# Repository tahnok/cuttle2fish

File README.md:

# Cuttle2Fish

Something you know (password) and something you have (cuttlefish shaped U2F token)

Based on the STM32F103

## Software

Intended to be based on https://github.com/gl-sergei/u2f-token

## Design Notes

https://github.com/tahnok/wiki/wiki/cuttle2fish

## Pictures

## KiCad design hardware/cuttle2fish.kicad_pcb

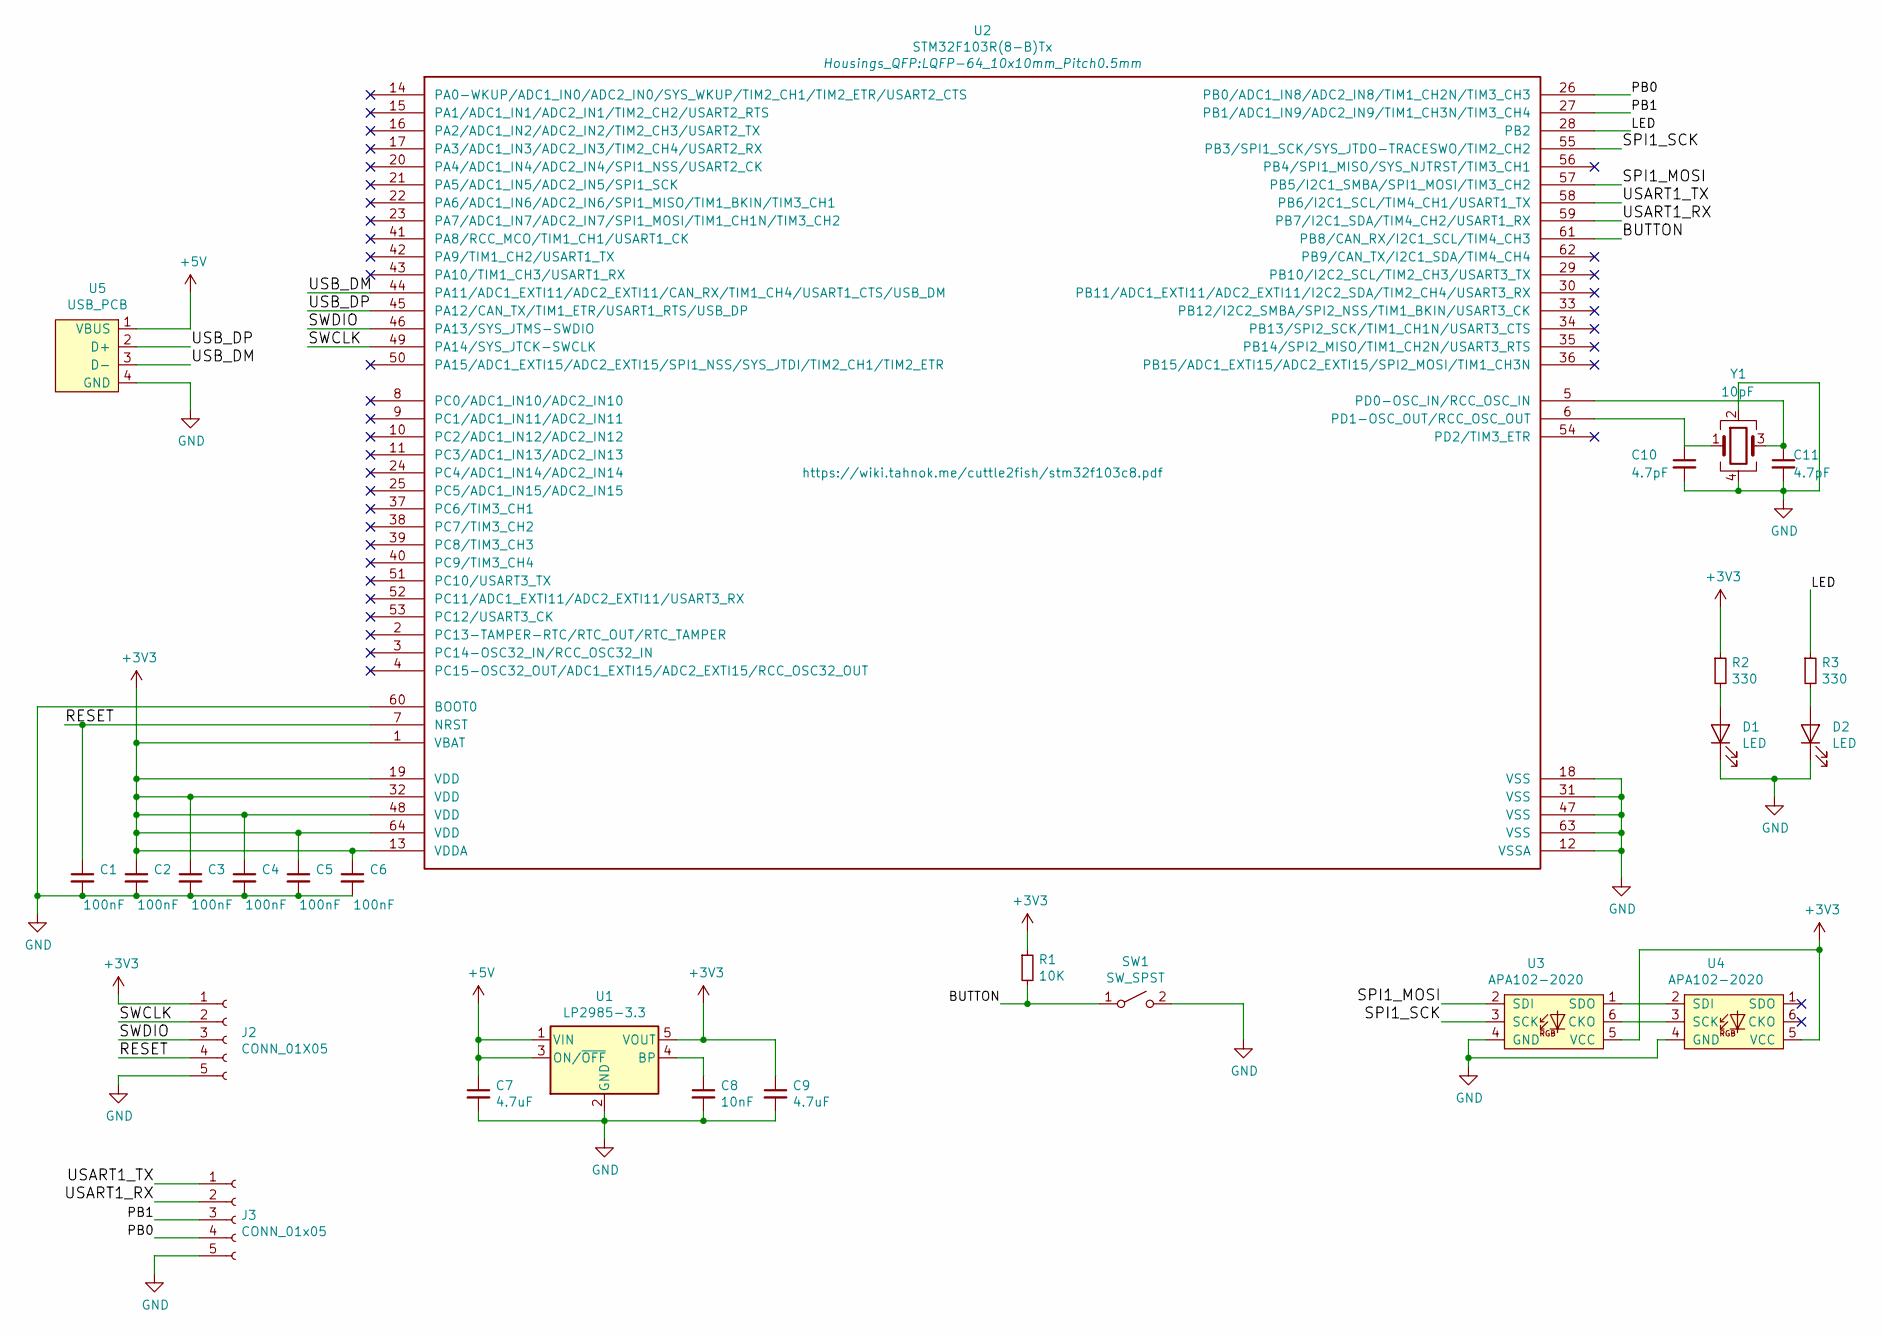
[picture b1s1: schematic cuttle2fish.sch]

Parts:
C1, C2, C3, C4, C5, C6: 100nF; C_0603
C7, C9: 4.7uF; C_0603
C8: 10nF; C_0603
C10, C11: 4.7pF; C_0603
D1, D2: LED; LED_0603
J2: CONN_01X05; Pin_Header_Straight_1x05_Pitch2.54mm
J3: CONN_01x05; Pin_Header_Straight_1x05_Pitch2.54mm
R1: 10K; R_0603
R2, R3: 330; R_0603
SW1: SW_SPST; SW_SPST_B3U-1000P
U1: LP2985-3.3; SOT-23-5
U2: STM32F103R(8-B)Tx; LQFP-64_10x10mm_Pitch0.5mm
U3, U4: APA102-2020
U5: USB_PCB; usb-PCB
Y1: 10pF; Crystal_SMD_5032-4pin_5.0x3.2mm

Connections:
+3V3: C2.1, C3.1, C4.1, C5.1, C6.1, C9.1, J2.1, R1.1, R2.1, U1.5 (VOUT), U2.1 (VBAT), U2.13 (VDDA), U2.19 (VDD), U2.32 (VDD), U2.48 (VDD), U2.64 (VDD), U3.5 (VCC), U4.5 (VCC)
+5V: C7.1, U1.1 (VIN), U1.3 (ON/~OFF~), U5.1 (VBUS)
/BUTTON: R1.2, SW1.1 (A), U2.61 (PB8/CAN_RX/I2C1_SCL/TIM4_CH3)
/LED: R3.1, U2.28 (PB2)
/PB0: J3.4, U2.26 (PB0/ADC1_IN8/ADC2_IN8/TIM1_CH2N/TIM3_CH3)
/PB1: J3.3, U2.27 (PB1/ADC1_IN9/ADC2_IN9/TIM1_CH3N/TIM3_CH4)
/RESET: C1.1, J2.4, U2.7 (NRST)
/SPI1_MOSI: U2.57 (PB5/I2C1_SMBA/SPI1_MOSI/TIM3_CH2), U3.2 (SDI)
/SPI1_SCK: U2.55 (PB3/SPI1_SCK/SYS_JTDO-TRACESWO/TIM2_CH2), U3.3 (SCK)
/SWCLK: J2.2, U2.49 (PA14/SYS_JTCK-SWCLK)
/SWDIO: J2.3, U2.46 (PA13/SYS_JTMS-SWDIO)
/USART1_RX: J3.2, U2.59 (PB7/I2C1_SDA/TIM4_CH2/USART1_RX)
/USART1_TX: J3.1, U2.58 (PB6/I2C1_SCL/TIM4_CH1/USART1_TX)
/USB_DM: U2.44 (PA11/ADC1_EXTI11/ADC2_EXTI11/CAN_RX/TIM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), U5.3 (D-)
/USB_DP: U2.45 (PA12/CAN_TX/TIM1_ETR/USART1_RTS/USB_DP), U5.2 (D+)
GND: C1.2, C2.2, C3.2, C4.2, C5.2, C6.2, C7.2, C8.2, C9.2, C10.2, C11.2, D1.1 (K), D2.1 (K), J2.5, J3.5, SW1.2 (B), U1.2 (GND), U2.12 (VSSA), U2.18 (VSS), U2.31 (VSS), U2.47 (VSS), U2.60 (BOOT0), U2.63 (VSS), U3.4 (GND), U4.4 (GND), U5.4 (GND), Y1.2, Y1.4
unnamed: C8.1, U1.4 (BP)
unnamed: C10.1, U2.6 (PD1-OSC_OUT/RCC_OSC_OUT), Y1.1
unnamed: C11.1, U2.5 (PD0-OSC_IN/RCC_OSC_IN), Y1.3
unnamed: D1.2 (A), R2.2
unnamed: D2.2 (A), R3.2
unnamed: U3.1 (SDO), U4.2 (SDI)
unnamed: U3.6 (CKO), U4.3 (SCK)

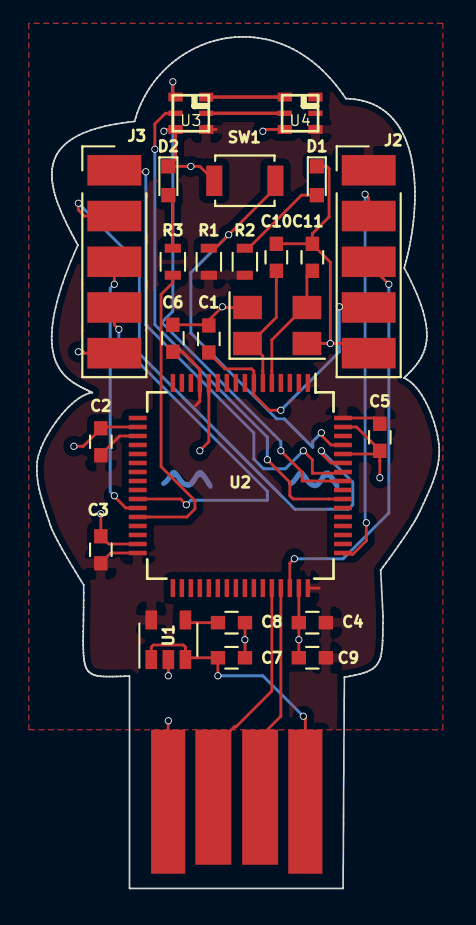
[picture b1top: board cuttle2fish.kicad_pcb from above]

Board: 2 copper layers, 22.4 x 47.3 mm, 26 parts (1 on the bottom side), 23 nets.

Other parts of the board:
svg2mod: G***; outline

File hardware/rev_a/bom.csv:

Reference,Quantity,Value,Footprint,
C11 C10,2,4.7pF,SMD 0603,https://www.digikey.ca/product-detail/en/CL10C4R7BB8NNNC/127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
C6 C5 C4 C3 C2 C1,6,100nF,SMD 0603,https://www.digikey.ca/product-detail/en/CC0603KRX7R7BB104/3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
C8,1,10nF,SMD 0603,https://www.digikey.ca/product-detail/en/CL10B103KB8NCNC/127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
C9 C7,2,4.7uF,SMD 0603,https://www.digikey.ca/product-detail/en/CL10A475MP5LNNC/127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
D1 D2,2,LED,SMD 0603,https://www.digikey.ca/product-detail/en/SML-D12U1WT86/SML-D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
R1,1,10K,SMD 0603,https://www.digikey.ca/product-detail/en/ESR03EZPF1002/RHM10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
R2 R3,2,330,SMD 0603,https://www.digikey.ca/product-detail/en/ESR03EZPJ331/RHM330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
SW1,1,B3U-1000P,B3U-1000P,https://www.digikey.ca/product-detail/en/B3U-1000P/SW1020CT-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
U1,1,LP2985-3.3,SMD SOT-23-5,https://www.digikey.ca/product-detail/en/LP2985-33DBVR/296-1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
U2,1,STM32F103R(8-B)Tx,LQFP 64 10x10mm Pitch0.5mm,https://www.digikey.ca/product-detail/en/STM32F103RBT7/497-1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
U3 U4,2,APA102-2020,APA102-2020,https://www.aliexpress.com/item/-/32856952551.html
Y1,1,10pF,SMD 5032,https://www.digikey.ca/product-detail/en/ECS-80-10-30B-CWN-T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

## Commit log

2018-11-11 Add skeleton kicad project
2018-11-20 add first pass at USB and power caps
2018-11-24 Update cuttle2fish.sch
    Add labels for pins we want to break out and programming connector
2018-11-25 Add APA102, button, PMIC
2018-11-25 remove test symbol lib
2018-11-25 Revert "remove test symbol lib"
    This reverts commit 6f75cef5a91738c681950cd6204f8edfb5d6b3d5.
2018-11-25 Rev 1 schematic
2018-11-25 rev 1 PDF
2018-11-25 Add APA102 footprint from great scott gadgets
    https://github.com/greatscottgadgets/gsg-kicad-lib/blob/master/gsg-modules.pretty/APA102-2020.kicad_mod
2018-11-25 Add LEDs and button footprint
2018-11-25 Add PCB USB footprint and symbol from USBArmory
    https://github.com/inversepath/usbarmory
2018-11-25 Updated RevA
2018-11-25 rename symbol file from test to symbols
2018-11-30 add outline footprint and start routing!
2018-12-01 Update schematic with missed connections...
2018-12-01 routing attempt #1 (bad)
2018-12-01 layout v2!
2018-12-01 tweak layout, expose eyes in outline
2018-12-01 rev A gerbers
2018-12-01 Add bom with digikey links
2018-12-21 stencils and readme with images
2019-02-10 blinky with platformio
